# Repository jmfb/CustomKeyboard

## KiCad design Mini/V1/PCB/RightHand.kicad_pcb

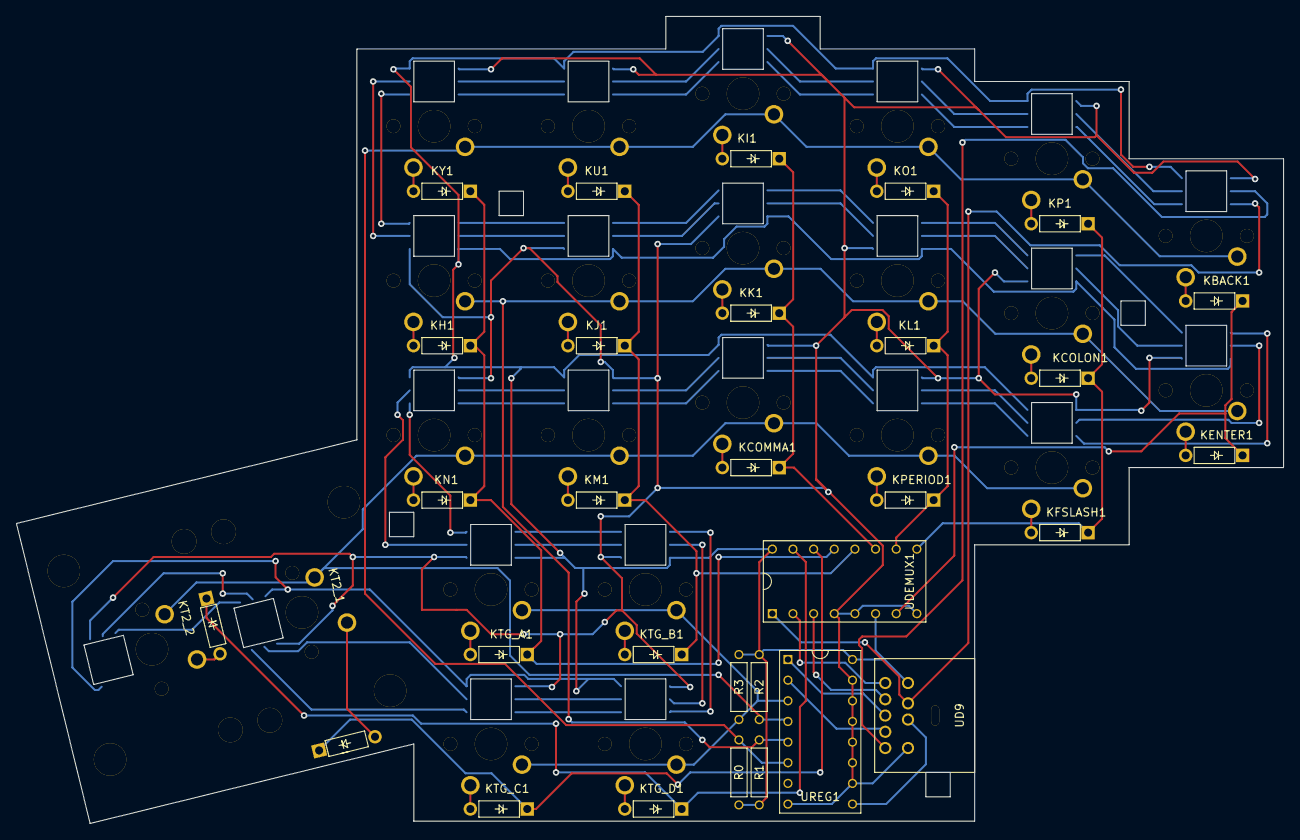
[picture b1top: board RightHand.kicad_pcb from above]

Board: 2 copper layers, 155.9 x 99.3 mm, 30 parts (0 on the bottom side), 88 nets.

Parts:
KBACK1: KeyLedDiode; KeyLedDiodeR2L
KCOLON1: KeyLedDiode; KeyLedDiodeL2R
KCOMMA1: KeyLedDiode; KeyLedDiodeR2L
KENTER1: KeyLedDiode; KeyLedDiodeL2R
KFSLASH1: KeyLedDiode; KeyLedDiodeR2L
KH1: KeyLedDiode; KeyLedDiodeL2R
KI1: KeyLedDiode; KeyLedDiodeR2L
KJ1: KeyLedDiode; KeyLedDiodeL2R
KK1: KeyLedDiode; KeyLedDiodeL2R
KL1: KeyLedDiode; KeyLedDiodeL2R
KM1: KeyLedDiode; KeyLedDiodeR2L
KN1: KeyLedDiode; KeyLedDiodeR2L
KO1: KeyLedDiode; KeyLedDiodeR2L
KP1: KeyLedDiode; KeyLedDiodeR2L
KPERIOD1: KeyLedDiode; KeyLedDiodeR2L
KT2_1: KeyLedDiode; Key2LedDiodeL2R
KT2_2: KeyLedDiode; Key2LedDiodeR2L
KTG_A1: KeyLedDiode; KeyLedDiodeL2R
KTG_B1: KeyLedDiode; KeyLedDiodeL2R
KTG_C1: KeyLedDiode; KeyLedDiodeR2L
KTG_D1: KeyLedDiode; KeyLedDiodeR2L
KU1: KeyLedDiode; KeyLedDiodeR2L
KY1: KeyLedDiode; KeyLedDiodeR2L
R0, R1, R2, R3: R; PullupResistor
UD9: MiniDINN9; MiniDin9
UDEMUX1: Demultiplexer; DualInlineMicrochip2x8
UREG1: ParallelLoadShiftRegister; DualInlineMicrochip2x8

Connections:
C0: KBACK1.1, KI1.1, KO1.1, KP1.1, KU1.1, KY1.1, R0.2, UREG1.6
C1: KCOLON1.1, KENTER1.1, KH1.1, KJ1.1, KK1.1, KL1.1, R1.1, UREG1.5
C2: KCOMMA1.1, KFSLASH1.1, KM1.1, KN1.1, KPERIOD1.1, KT2_1.1, KT2_2.1, R2.1, UREG1.4
C3: KTG_A1.1, KTG_B1.1, KTG_C1.1, KTG_D1.1, R3.1, UREG1.3
CLK_C: UD9.8, UREG1.2
CLK_L: KBACK1.9, UD9.9
GND: KBACK1.8, KCOLON1.8, KCOMMA1.8, KENTER1.8, KFSLASH1.8, KH1.8, KI1.8, KJ1.8, KK1.8, KL1.8, KM1.8, KN1.8, KO1.8, KP1.8, KPERIOD1.8, KT2_1.8, KT2_2.8, KTG_A1.8, KTG_B1.8, KTG_C1.8, KTG_D1.8, KU1.8, KY1.8, UD9.6, UDEMUX1.4, UDEMUX1.5, UDEMUX1.8, UREG1.8, UREG1.10, UREG1.11, UREG1.12, UREG1.13, UREG1.14, UREG1.15
unnamed: KBACK1.2, KBACK1.3
unnamed: KBACK1.6, KP1.9
unnamed: KBACK1.7, KP1.10
unnamed: KCOMMA1.2, KCOMMA1.3
unnamed: KCOMMA1.6, KM1.9
unnamed: KCOMMA1.7, KM1.10
unnamed: KCOMMA1.9, KPERIOD1.6
unnamed: KCOMMA1.10, KPERIOD1.7
unnamed: KENTER1.2, KENTER1.3
unnamed: KENTER1.6, KFSLASH1.9
unnamed: KENTER1.7, KFSLASH1.10
unnamed: KCOLON1.6, KENTER1.9
unnamed: KCOLON1.7, KENTER1.10
unnamed: KFSLASH1.2, KFSLASH1.3
unnamed: KFSLASH1.6, KPERIOD1.9
unnamed: KFSLASH1.7, KPERIOD1.10
unnamed: KH1.2, KH1.3
unnamed: KH1.6, KJ1.9
unnamed: KH1.7, KJ1.10
unnamed: KH1.9, KY1.6
unnamed: KH1.10, KY1.7
unnamed: KI1.2, KI1.3
unnamed: KI1.6, KU1.9
unnamed: KI1.7, KU1.10
unnamed: KI1.9, KO1.6
unnamed: KI1.10, KO1.7
unnamed: KJ1.2, KJ1.3
unnamed: KJ1.6, KK1.9
unnamed: KJ1.7, KK1.10
unnamed: KK1.2, KK1.3
unnamed: KK1.6, KL1.9
unnamed: KK1.7, KL1.10
unnamed: KL1.2, KL1.3
unnamed: KCOLON1.9, KL1.6
unnamed: KCOLON1.10, KL1.7
unnamed: KM1.2, KM1.3
unnamed: KM1.6, KN1.9
unnamed: KM1.7, KN1.10
unnamed: KN1.2, KN1.3
unnamed: KN1.6, KTG_A1.9
unnamed: KN1.7, KTG_A1.10
unnamed: KO1.2, KO1.3
unnamed: KO1.9, KP1.6
unnamed: KO1.10, KP1.7
unnamed: KP1.2, KP1.3
unnamed: KPERIOD1.2, KPERIOD1.3
unnamed: KCOLON1.2, KCOLON1.3
unnamed: KT2_1.2, KT2_1.3
unnamed: KT2_1.6, KT2_2.9
unnamed: KT2_1.7, KT2_2.10
unnamed: KT2_1.9, KTG_C1.6
unnamed: KT2_1.10, KTG_C1.7
unnamed: KT2_2.2, KT2_2.3
unnamed: KTG_A1.2, KTG_A1.3
unnamed: KTG_A1.6, KTG_B1.9
unnamed: KTG_A1.7, KTG_B1.10
unnamed: KTG_B1.2, KTG_B1.3
unnamed: KTG_B1.6, KTG_D1.9
unnamed: KTG_B1.7, KTG_D1.10
unnamed: KTG_C1.2, KTG_C1.3
unnamed: KTG_C1.9, KTG_D1.6
unnamed: KTG_C1.10, KTG_D1.7
unnamed: KTG_D1.2, KTG_D1.3
unnamed: KU1.2, KU1.3
unnamed: KU1.6, KY1.9
unnamed: KU1.7, KY1.10
unnamed: KY1.2, KY1.3
R0: KT2_2.4, KTG_D1.4, UDEMUX1.15
R1: KT2_1.4, KTG_C1.4, UDEMUX1.14
R2: KH1.4, KN1.4, KTG_A1.4, KY1.4, UDEMUX1.13
R3: KJ1.4, KM1.4, KTG_B1.4, KU1.4, UDEMUX1.12
R4: KCOMMA1.4, KI1.4, KK1.4, UDEMUX1.11
R5: KL1.4, KO1.4, KPERIOD1.4, UDEMUX1.10
R6: KCOLON1.4, KFSLASH1.4, KP1.4, UDEMUX1.9
R7: KBACK1.4, KENTER1.4, UDEMUX1.7
RX: UD9.2, UREG1.9
S0_DL: KBACK1.10, UD9.1, UDEMUX1.1
S1: UD9.7, UDEMUX1.2
S2: UD9.4, UDEMUX1.3
SH_LD: UD9.5, UREG1.1
VCC: KBACK1.5, KCOLON1.5, KCOMMA1.5, KENTER1.5, KFSLASH1.5, KH1.5, KI1.5, KJ1.5, KK1.5, KL1.5, KM1.5, KN1.5, KO1.5, KP1.5, KPERIOD1.5, KT2_1.5, KT2_2.5, KTG_A1.5, KTG_B1.5, KTG_C1.5, KTG_D1.5, KU1.5, KY1.5, R0.1, R1.2, R2.2, R3.2, UD9.3, UDEMUX1.6, UDEMUX1.16, UREG1.16

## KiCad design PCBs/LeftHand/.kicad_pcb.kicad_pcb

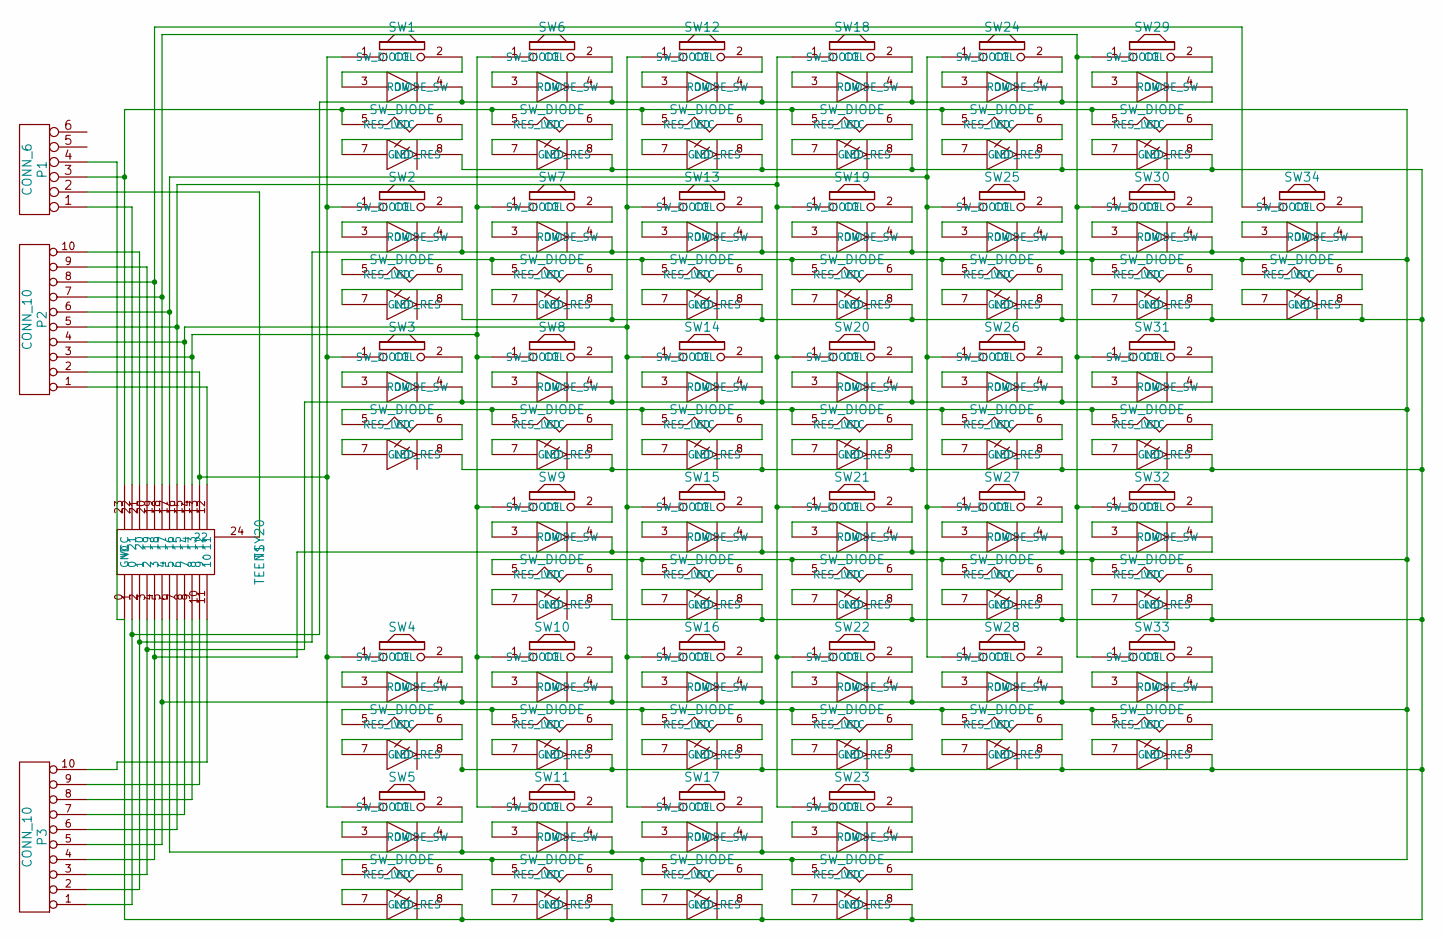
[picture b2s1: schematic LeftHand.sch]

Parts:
P1: CONN_6
P2, P3: CONN_10
SW1, SW2, SW3, SW4, SW5, SW6, SW7, SW8, SW9, SW10, SW11, SW12, SW13, SW14, SW15, SW16, SW17, SW18, SW19, SW20, SW21, SW22, SW23, SW24, SW25, SW26, SW27, SW28, SW29, SW30, SW31, SW32, SW33, SW34: SW_DIODE
T1: TEENSY20

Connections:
unnamed: P3.4, SW9.4 (ROW), SW15.4 (ROW), SW21.4 (ROW), SW27.4 (ROW), SW32.4 (ROW), T1.4 (3)
unnamed: SW5.4 (ROW), SW11.4 (ROW), SW17.4 (ROW), SW23.4 (ROW), T1.6 (5)
unnamed: P3.5, SW4.4 (ROW), SW10.4 (ROW), SW16.4 (ROW), SW22.4 (ROW), SW28.4 (ROW), SW33.4 (ROW), T1.5 (4)
unnamed: P3.3, SW3.4 (ROW), SW8.4 (ROW), SW14.4 (ROW), SW20.4 (ROW), SW26.4 (ROW), SW31.4 (ROW), T1.3 (2)
unnamed: SW11.6 (RES_LED), SW11.7 (LED_RES)
unnamed: SW5.2 (SW_DIODE), SW5.3 (DIODE_SW)
unnamed: SW5.6 (RES_LED), SW5.7 (LED_RES)
unnamed: SW10.2 (SW_DIODE), SW10.3 (DIODE_SW)
unnamed: SW10.6 (RES_LED), SW10.7 (LED_RES)
unnamed: SW11.2 (SW_DIODE), SW11.3 (DIODE_SW)
unnamed: SW16.2 (SW_DIODE), SW16.3 (DIODE_SW)
unnamed: SW16.6 (RES_LED), SW16.7 (LED_RES)
unnamed: SW17.2 (SW_DIODE), SW17.3 (DIODE_SW)
unnamed: SW17.6 (RES_LED), SW17.7 (LED_RES)
unnamed: SW30.6 (RES_LED), SW30.7 (LED_RES)
unnamed: SW31.2 (SW_DIODE), SW31.3 (DIODE_SW)
unnamed: SW31.6 (RES_LED), SW31.7 (LED_RES)
unnamed: SW32.2 (SW_DIODE), SW32.3 (DIODE_SW)
unnamed: SW32.6 (RES_LED), SW32.7 (LED_RES)
unnamed: SW34.2 (SW_DIODE), SW34.3 (DIODE_SW)
unnamed: SW34.6 (RES_LED), SW34.7 (LED_RES)
unnamed: SW4.2 (SW_DIODE), SW4.3 (DIODE_SW)
unnamed: SW4.6 (RES_LED), SW4.7 (LED_RES)
unnamed: SW28.2 (SW_DIODE), SW28.3 (DIODE_SW)
unnamed: SW22.2 (SW_DIODE), SW22.3 (DIODE_SW)
unnamed: SW22.6 (RES_LED), SW22.7 (LED_RES)
unnamed: SW23.2 (SW_DIODE), SW23.3 (DIODE_SW)
unnamed: SW23.6 (RES_LED), SW23.7 (LED_RES)
unnamed: SW28.6 (RES_LED), SW28.7 (LED_RES)
unnamed: SW33.2 (SW_DIODE), SW33.3 (DIODE_SW)
unnamed: SW33.6 (RES_LED), SW33.7 (LED_RES)
unnamed: P2.8, SW34.1 (COL), T1.19 (18)
unnamed: P2.10, T1.21 (20)
unnamed: P2.9, T1.20 (19)
unnamed: P1.1, T1.22 (21)
unnamed: P1.2, T1.24 (22)
unnamed: P3.7, T1.8 (7)
unnamed: P3.6, T1.7 (6)
unnamed: P3.8, T1.9 (8)
unnamed: P3.9, T1.10 (9)
unnamed: P3.10, T1.11 (10)
unnamed: P2.1, T1.12 (11)
unnamed: P3.1, SW1.4 (ROW), SW6.4 (ROW), SW12.4 (ROW), SW18.4 (ROW), SW24.4 (ROW), SW29.4 (ROW), T1.1 (0)
unnamed: P2.7, SW29.1 (COL), SW30.1 (COL), SW31.1 (COL), SW32.1 (COL), SW33.1 (COL), T1.18 (17)
unnamed: P3.2, SW2.4 (ROW), SW7.4 (ROW), SW13.4 (ROW), SW19.4 (ROW), SW25.4 (ROW), SW30.4 (ROW), SW34.4 (ROW), T1.2 (1)
unnamed: P2.6, SW24.1 (COL), SW25.1 (COL), SW26.1 (COL), SW27.1 (COL), SW28.1 (COL), T1.17 (16)
unnamed: P1.3, SW1.5 (VCC), SW2.5 (VCC), SW3.5 (VCC), SW4.5 (VCC), SW5.5 (VCC), SW6.5 (VCC), SW7.5 (VCC), SW8.5 (VCC), SW9.5 (VCC), SW10.5 (VCC), SW11.5 (VCC), SW12.5 (VCC), SW13.5 (VCC), SW14.5 (VCC), SW15.5 (VCC), SW16.5 (VCC), SW17.5 (VCC), SW18.5 (VCC), SW19.5 (VCC), SW20.5 (VCC), SW21.5 (VCC), SW22.5 (VCC), SW23.5 (VCC), SW24.5 (VCC), SW25.5 (VCC), SW26.5 (VCC), SW27.5 (VCC), SW28.5 (VCC), SW29.5 (VCC), SW30.5 (VCC), SW31.5 (VCC), SW32.5 (VCC), SW33.5 (VCC), SW34.5 (VCC), T1.23 (VCC)
unnamed: P2.3, SW6.1 (COL), SW7.1 (COL), SW8.1 (COL), SW9.1 (COL), SW10.1 (COL), SW11.1 (COL), T1.14 (13)
unnamed: P2.2, SW1.1 (COL), SW2.1 (COL), SW3.1 (COL), SW4.1 (COL), SW5.1 (COL), T1.13 (12)
unnamed: P2.5, SW18.1 (COL), SW19.1 (COL), SW20.1 (COL), SW21.1 (COL), SW22.1 (COL), SW23.1 (COL), T1.16 (15)
unnamed: P2.4, SW12.1 (COL), SW13.1 (COL), SW14.1 (COL), SW15.1 (COL), SW16.1 (COL), SW17.1 (COL), T1.15 (14)
unnamed: SW20.2 (SW_DIODE), SW20.3 (DIODE_SW)
unnamed: SW18.6 (RES_LED), SW18.7 (LED_RES)
unnamed: SW19.2 (SW_DIODE), SW19.3 (DIODE_SW)
unnamed: SW19.6 (RES_LED), SW19.7 (LED_RES)
unnamed: SW20.6 (RES_LED), SW20.7 (LED_RES)
unnamed: SW21.2 (SW_DIODE), SW21.3 (DIODE_SW)
unnamed: SW21.6 (RES_LED), SW21.7 (LED_RES)
unnamed: SW15.2 (SW_DIODE), SW15.3 (DIODE_SW)
unnamed: SW15.6 (RES_LED), SW15.7 (LED_RES)
unnamed: SW18.2 (SW_DIODE), SW18.3 (DIODE_SW)
unnamed: SW25.6 (RES_LED), SW25.7 (LED_RES)
unnamed: SW26.2 (SW_DIODE), SW26.3 (DIODE_SW)
unnamed: SW26.6 (RES_LED), SW26.7 (LED_RES)
unnamed: SW27.6 (RES_LED), SW27.7 (LED_RES)
unnamed: SW24.2 (SW_DIODE), SW24.3 (DIODE_SW)
unnamed: SW24.6 (RES_LED), SW24.7 (LED_RES)
unnamed: SW25.2 (SW_DIODE), SW25.3 (DIODE_SW)
unnamed: SW6.2 (SW_DIODE), SW6.3 (DIODE_SW)
unnamed: SW6.6 (RES_LED), SW6.7 (LED_RES)
unnamed: SW7.6 (RES_LED), SW7.7 (LED_RES)
unnamed: SW1.2 (SW_DIODE), SW1.3 (DIODE_SW)
unnamed: SW1.6 (RES_LED), SW1.7 (LED_RES)
unnamed: SW2.2 (SW_DIODE), SW2.3 (DIODE_SW)
unnamed: SW2.6 (RES_LED), SW2.7 (LED_RES)
unnamed: SW3.2 (SW_DIODE), SW3.3 (DIODE_SW)
unnamed: SW3.6 (RES_LED), SW3.7 (LED_RES)
unnamed: SW13.2 (SW_DIODE), SW13.3 (DIODE_SW)
unnamed: SW12.2 (SW_DIODE), SW12.3 (DIODE_SW)
unnamed: SW12.6 (RES_LED), SW12.7 (LED_RES)
unnamed: SW13.6 (RES_LED), SW13.7 (LED_RES)
unnamed: SW14.2 (SW_DIODE), SW14.3 (DIODE_SW)
unnamed: SW14.6 (RES_LED), SW14.7 (LED_RES)
unnamed: SW8.2 (SW_DIODE), SW8.3 (DIODE_SW)
unnamed: SW8.6 (RES_LED), SW8.7 (LED_RES)
unnamed: SW9.2 (SW_DIODE), SW9.3 (DIODE_SW)
unnamed: SW9.6 (RES_LED), SW9.7 (LED_RES)
unnamed: SW7.2 (SW_DIODE), SW7.3 (DIODE_SW)
unnamed: SW27.2 (SW_DIODE), SW27.3 (DIODE_SW)
unnamed: SW29.2 (SW_DIODE), SW29.3 (DIODE_SW)
unnamed: SW29.6 (RES_LED), SW29.7 (LED_RES)
unnamed: SW30.2 (SW_DIODE), SW30.3 (DIODE_SW)

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
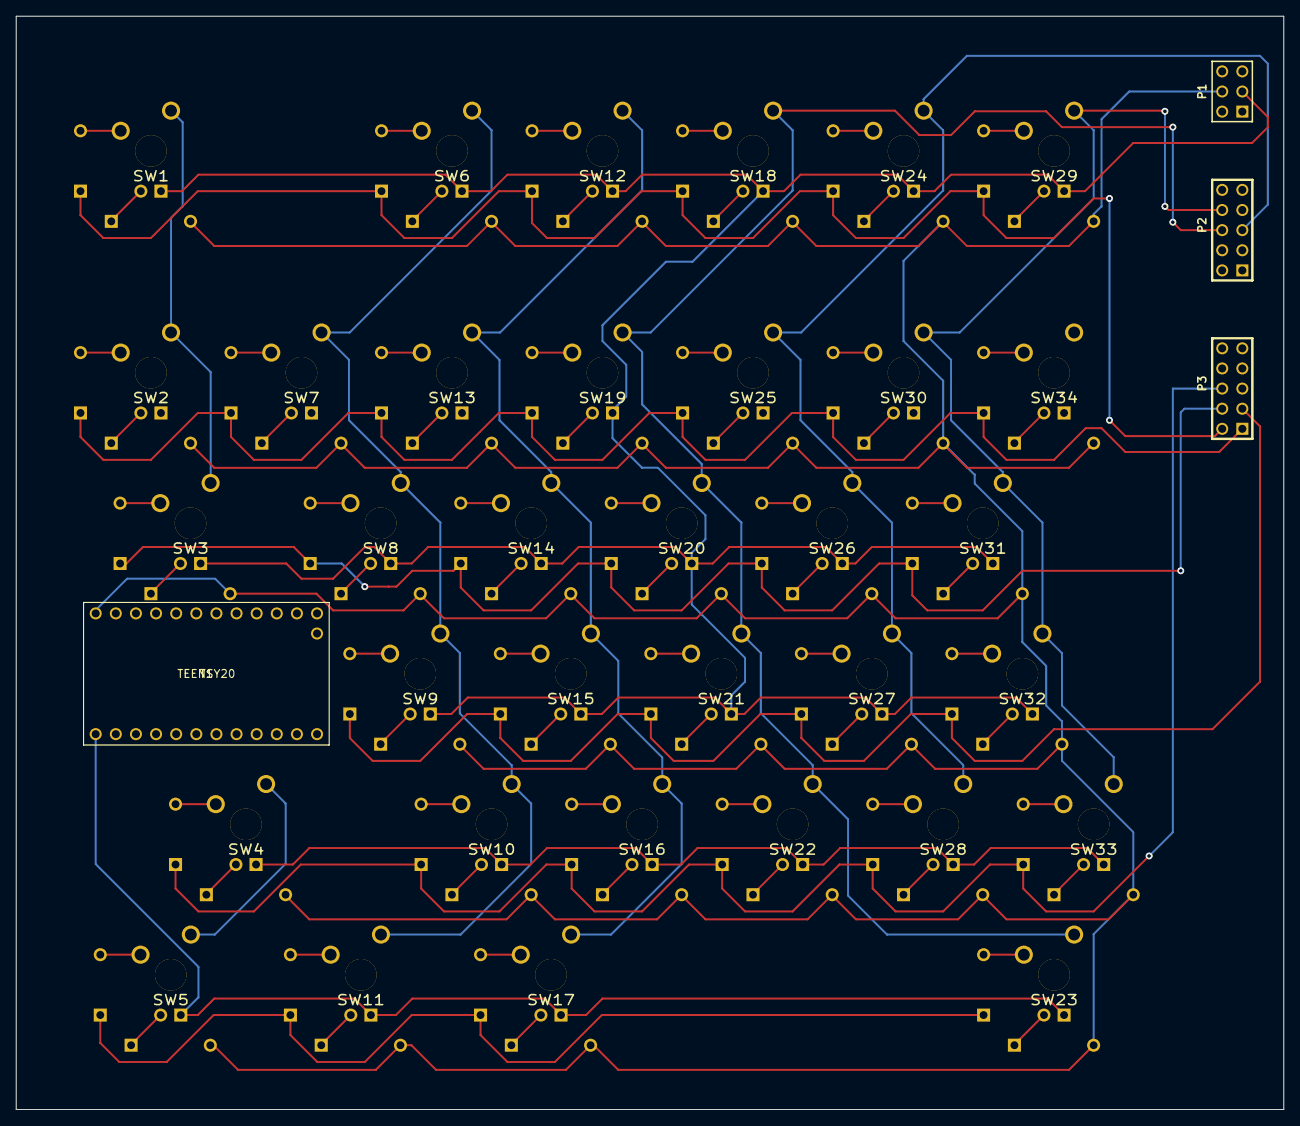
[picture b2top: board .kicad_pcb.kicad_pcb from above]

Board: 2 copper layers, 160.0 x 138.0 mm, 38 parts (0 on the bottom side), 94 nets.

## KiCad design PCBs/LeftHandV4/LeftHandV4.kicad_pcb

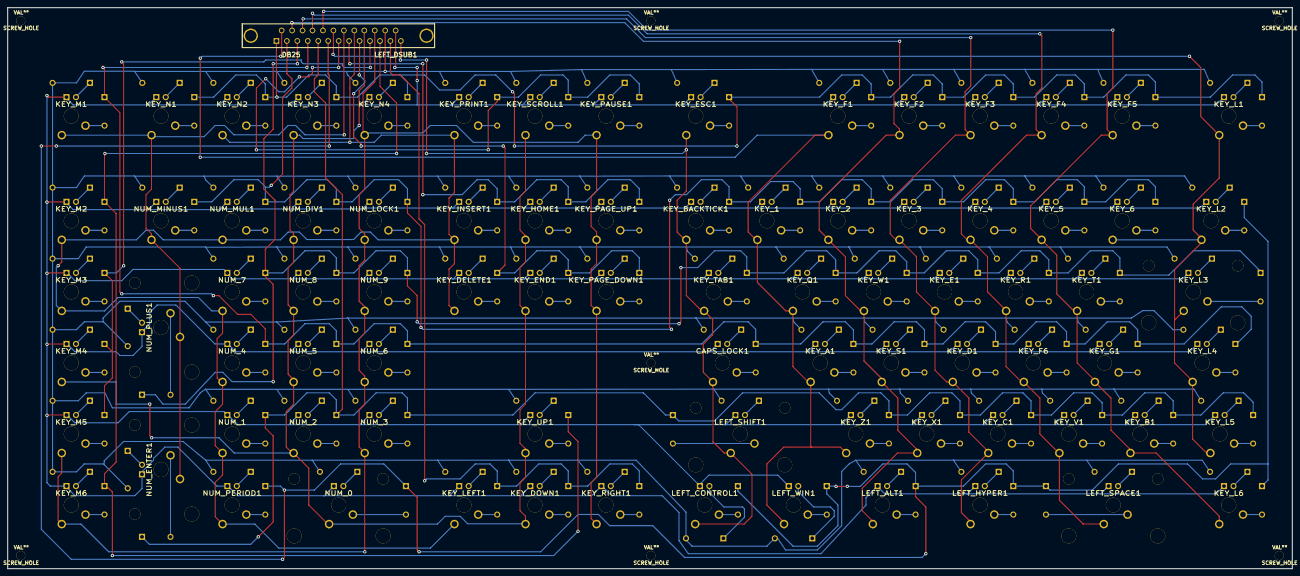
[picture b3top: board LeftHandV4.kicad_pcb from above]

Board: 2 copper layers, 343.5 x 150.0 mm, 90 parts (0 on the bottom side), 189 nets.

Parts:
CAPS_LOCK1: SW_DIODE
KEY_1, KEY_2, KEY_3, KEY_4, KEY_5, KEY_6: SW_DIODE
KEY_A1: SW_DIODE
KEY_B1: SW_DIODE
KEY_BACKTICK1: SW_DIODE
KEY_C1: SW_DIODE
KEY_D1: SW_DIODE
KEY_DELETE1: SW_DIODE
KEY_DOWN1: SW_DIODE
KEY_E1: SW_DIODE
KEY_END1: SW_DIODE
KEY_ESC1: SW_DIODE
KEY_F1, KEY_F2, KEY_F3, KEY_F4, KEY_F5, KEY_F6: SW_DIODE
KEY_G1: SW_DIODE
KEY_HOME1: SW_DIODE
KEY_INSERT1: SW_DIODE
KEY_L1, KEY_L2, KEY_L4, KEY_L5, KEY_L6: SW_DIODE
KEY_L3: SW_DIODE; SW2_DIODE_R
KEY_LEFT1: SW_DIODE
KEY_M1, KEY_M2, KEY_M3, KEY_M4, KEY_M5, KEY_M6: SW_DIODE
KEY_N1, KEY_N2, KEY_N3, KEY_N4: SW_DIODE
KEY_PAGE_DOWN1: SW_DIODE
KEY_PAGE_UP1: SW_DIODE
KEY_PAUSE1: SW_DIODE
KEY_PRINT1: SW_DIODE
KEY_Q1: SW_DIODE
KEY_R1: SW_DIODE
KEY_RIGHT1: SW_DIODE
KEY_S1: SW_DIODE
KEY_SCROLL1: SW_DIODE
KEY_T1: SW_DIODE
KEY_TAB1: SW_DIODE
KEY_UP1: SW_DIODE
KEY_V1: SW_DIODE
KEY_W1: SW_DIODE
KEY_X1: SW_DIODE
KEY_Z1: SW_DIODE
LEFT_ALT1: SW_DIODE
LEFT_CONTROL1: SW_DIODE; SW_DIODE_RTOP
LEFT_DSUB1: DB25; DB25FD
LEFT_HYPER1: SW_DIODE
LEFT_SHIFT1: SW_DIODE; SW2_DIODE_L
LEFT_SPACE1: SW_DIODE; SW2_DIODE_L
LEFT_WIN1: SW_DIODE; SW_DIODE_RTOP
NUM_0: SW_DIODE; SW2_DIODE_R
NUM_1, NUM_2, NUM_3, NUM_4, NUM_5, NUM_6, NUM_7, NUM_8, NUM_9: SW_DIODE
NUM_DIV1: SW_DIODE
NUM_ENTER1: SW_DIODE; SW2_DIODE_L
NUM_LOCK1: SW_DIODE
NUM_MINUS1: SW_DIODE
NUM_MUL1: SW_DIODE
NUM_PERIOD1: SW_DIODE
NUM_PLUS1: SW_DIODE; SW2_DIODE_L
SCREW_HOLE: VAL**; SCREW_HOLE
SCREW_HOLE#2, SCREW_HOLE#3, SCREW_HOLE#4, SCREW_HOLE#5, SCREW_HOLE#6, SCREW_HOLE#7: VAL**; SCREW_HOLE

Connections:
unnamed: LEFT_SPACE1.6, LEFT_SPACE1.7
unnamed: KEY_L6.2, KEY_L6.3
unnamed: KEY_L6.6, KEY_L6.7
unnamed: CAPS_LOCK1.8, KEY_1.8, KEY_2.8, KEY_3.8, KEY_4.8, KEY_5.8, KEY_6.8, KEY_A1.8, KEY_B1.8, KEY_BACKTICK1.8, KEY_C1.8, KEY_D1.8, KEY_DELETE1.8, KEY_DOWN1.8, KEY_E1.8, KEY_END1.8, KEY_ESC1.8, KEY_F1.8, KEY_F2.8, KEY_F3.8, KEY_F4.8, KEY_F5.8, KEY_F6.8, KEY_G1.8, KEY_HOME1.8, KEY_INSERT1.8, KEY_L1.8, KEY_L2.8, KEY_L3.8, KEY_L4.8, KEY_L5.8, KEY_L6.8, KEY_LEFT1.8, KEY_M1.8, KEY_M2.8, KEY_M3.8, KEY_M4.8, KEY_M5.8, KEY_M6.8, KEY_N1.8, KEY_N2.8, KEY_N3.8, KEY_N4.8, KEY_PAGE_DOWN1.8, KEY_PAGE_UP1.8, KEY_PAUSE1.8, KEY_PRINT1.8, KEY_Q1.8, KEY_R1.8, KEY_RIGHT1.8, KEY_S1.8, KEY_SCROLL1.8, KEY_T1.8, KEY_TAB1.8, KEY_UP1.8, KEY_V1.8, KEY_W1.8, KEY_X1.8, KEY_Z1.8, LEFT_ALT1.8, LEFT_CONTROL1.8, LEFT_DSUB1.25, LEFT_HYPER1.8, LEFT_SHIFT1.8, LEFT_SPACE1.8, LEFT_WIN1.8, NUM_0.8, NUM_1.8, NUM_2.8, NUM_3.8, NUM_4.8, NUM_5.8, NUM_6.8, NUM_7.8, NUM_8.8, NUM_9.8, NUM_DIV1.8, NUM_ENTER1.8, NUM_LOCK1.8, NUM_MINUS1.8, NUM_MUL1.8, NUM_PERIOD1.8, NUM_PLUS1.8
unnamed: KEY_ESC1.4, KEY_F1.4, KEY_F2.4, KEY_F3.4, KEY_F4.4, KEY_F5.4, KEY_L1.4, KEY_N1.4, KEY_N2.4, KEY_N3.4, KEY_N4.4, LEFT_DSUB1.1
unnamed: KEY_1.4, KEY_2.4, KEY_3.4, KEY_4.4, KEY_5.4, KEY_6.4, KEY_BACKTICK1.4, LEFT_DSUB1.2, NUM_DIV1.4, NUM_LOCK1.4, NUM_MINUS1.4, NUM_MUL1.4
unnamed: KEY_E1.4, KEY_L3.4, KEY_Q1.4, KEY_R1.4, KEY_T1.4, KEY_TAB1.4, KEY_W1.4, LEFT_DSUB1.3, NUM_7.4, NUM_8.4, NUM_9.4, NUM_PLUS1.4
unnamed: CAPS_LOCK1.4, KEY_A1.4, KEY_D1.4, KEY_F6.4, KEY_G1.4, KEY_L4.4, KEY_M1.4, KEY_S1.4, LEFT_DSUB1.4, NUM_4.4, NUM_5.4, NUM_6.4
unnamed: NUM_ENTER1.6, NUM_ENTER1.7
unnamed: KEY_M5.2, KEY_M5.3
unnamed: KEY_M5.6, KEY_M5.7
unnamed: KEY_M6.2, KEY_M6.3
unnamed: KEY_M6.6, KEY_M6.7
unnamed: NUM_ENTER1.2, NUM_ENTER1.3
unnamed: NUM_4.2, NUM_4.3
unnamed: NUM_4.6, NUM_4.7
unnamed: NUM_1.2, NUM_1.3
unnamed: NUM_1.6, NUM_1.7
unnamed: NUM_9.2, NUM_9.3
unnamed: NUM_9.6, NUM_9.7
unnamed: KEY_DELETE1.2, KEY_DELETE1.3
unnamed: KEY_DELETE1.6, KEY_DELETE1.7
unnamed: KEY_END1.2, KEY_END1.3
unnamed: NUM_PERIOD1.2, NUM_PERIOD1.3
unnamed: KEY_END1.6, KEY_END1.7
unnamed: KEY_PAGE_DOWN1.2, KEY_PAGE_DOWN1.3
unnamed: KEY_PAGE_DOWN1.6, KEY_PAGE_DOWN1.7
unnamed: KEY_M4.2, KEY_M4.3
unnamed: KEY_M4.6, KEY_M4.7
unnamed: KEY_UP1.6, KEY_UP1.7
unnamed: NUM_0.2, NUM_0.3
unnamed: NUM_0.6, NUM_0.7
unnamed: KEY_LEFT1.2, KEY_LEFT1.3
unnamed: KEY_LEFT1.6, KEY_LEFT1.7
unnamed: KEY_UP1.2, KEY_UP1.3
unnamed: KEY_DOWN1.2, KEY_DOWN1.3
unnamed: KEY_DOWN1.6, KEY_DOWN1.7
unnamed: KEY_RIGHT1.2, KEY_RIGHT1.3
unnamed: KEY_RIGHT1.6, KEY_RIGHT1.7
unnamed: KEY_ESC1.2, KEY_ESC1.3
unnamed: NUM_2.6, NUM_2.7
unnamed: NUM_PERIOD1.6, NUM_PERIOD1.7
unnamed: NUM_5.2, NUM_5.3
unnamed: NUM_5.6, NUM_5.7
unnamed: NUM_2.2, NUM_2.3
unnamed: NUM_6.2, NUM_6.3
unnamed: NUM_6.6, NUM_6.7
unnamed: NUM_3.2, NUM_3.3
unnamed: NUM_3.6, NUM_3.7
unnamed: KEY_SCROLL1.6, KEY_SCROLL1.7
unnamed: KEY_N1.6, KEY_N1.7
unnamed: KEY_N2.6, KEY_N2.7
unnamed: KEY_N3.6, KEY_N3.7
unnamed: KEY_N4.6, KEY_N4.7
unnamed: KEY_PRINT1.6, KEY_PRINT1.7
unnamed: KEY_PAUSE1.6, KEY_PAUSE1.7
unnamed: KEY_M2.2, KEY_M2.3
unnamed: KEY_M2.6, KEY_M2.7
unnamed: NUM_MINUS1.2, NUM_MINUS1.3
unnamed: NUM_MINUS1.6, NUM_MINUS1.7
unnamed: KEY_N4.2, KEY_N4.3
unnamed: CAPS_LOCK1.5, KEY_1.5, KEY_2.5, KEY_3.5, KEY_4.5, KEY_5.5, KEY_6.5, KEY_A1.5, KEY_B1.5, KEY_BACKTICK1.5, KEY_C1.5, KEY_D1.5, KEY_DELETE1.5, KEY_DOWN1.5, KEY_E1.5, KEY_END1.5, KEY_ESC1.5, KEY_F1.5, KEY_F2.5, KEY_F3.5, KEY_F4.5, KEY_F5.5, KEY_F6.5, KEY_G1.5, KEY_HOME1.5, KEY_INSERT1.5, KEY_L1.5, KEY_L2.5, KEY_L3.5, KEY_L4.5, KEY_L5.5, KEY_L6.5, KEY_LEFT1.5, KEY_M1.5, KEY_M2.5, KEY_M3.5, KEY_M4.5, KEY_M5.5, KEY_M6.5, KEY_N1.5, KEY_N2.5, KEY_N3.5, KEY_N4.5, KEY_PAGE_DOWN1.5, KEY_PAGE_UP1.5, KEY_PAUSE1.5, KEY_PRINT1.5, KEY_Q1.5, KEY_R1.5, KEY_RIGHT1.5, KEY_S1.5, KEY_SCROLL1.5, KEY_T1.5, KEY_TAB1.5, KEY_UP1.5, KEY_V1.5, KEY_W1.5, KEY_X1.5, KEY_Z1.5, LEFT_ALT1.5, LEFT_CONTROL1.5, LEFT_DSUB1.24, LEFT_HYPER1.5, LEFT_SHIFT1.5, LEFT_SPACE1.5, LEFT_WIN1.5, NUM_0.5, NUM_1.5, NUM_2.5, NUM_3.5, NUM_4.5, NUM_5.5, NUM_6.5, NUM_7.5, NUM_8.5, NUM_9.5, NUM_DIV1.5, NUM_ENTER1.5, NUM_LOCK1.5, NUM_MINUS1.5, NUM_MUL1.5, NUM_PERIOD1.5, NUM_PLUS1.5
unnamed: KEY_M1.2, KEY_M1.3
unnamed: KEY_N1.2, KEY_N1.3
unnamed: KEY_N2.2, KEY_N2.3
unnamed: KEY_N3.2, KEY_N3.3
unnamed: KEY_PRINT1.2, KEY_PRINT1.3
unnamed: KEY_SCROLL1.2, KEY_SCROLL1.3
unnamed: KEY_PAUSE1.2, KEY_PAUSE1.3
unnamed: KEY_M1.6, KEY_M1.7
unnamed: KEY_HOME1.6, KEY_HOME1.7
unnamed: KEY_PAGE_UP1.2, KEY_PAGE_UP1.3
unnamed: KEY_PAGE_UP1.6, KEY_PAGE_UP1.7
unnamed: KEY_M3.2, KEY_M3.3
unnamed: KEY_M3.6, KEY_M3.7
unnamed: NUM_PLUS1.2, NUM_PLUS1.3
unnamed: NUM_7.2, NUM_7.3
unnamed: NUM_7.6, NUM_7.7
unnamed: NUM_PLUS1.6, NUM_PLUS1.7
unnamed: NUM_8.2, NUM_8.3
unnamed: NUM_8.6, NUM_8.7
unnamed: NUM_LOCK1.2, NUM_LOCK1.3
unnamed: NUM_MUL1.2, NUM_MUL1.3
unnamed: NUM_MUL1.6, NUM_MUL1.7
unnamed: NUM_DIV1.2, NUM_DIV1.3
unnamed: NUM_DIV1.6, NUM_DIV1.7
unnamed: NUM_LOCK1.6, NUM_LOCK1.7
unnamed: KEY_INSERT1.2, KEY_INSERT1.3
unnamed: KEY_INSERT1.6, KEY_INSERT1.7
unnamed: KEY_HOME1.2, KEY_HOME1.3
unnamed: KEY_L4.2, KEY_L4.3
unnamed: KEY_D1.6, KEY_D1.7
unnamed: KEY_F6.2, KEY_F6.3
unnamed: KEY_F6.6, KEY_F6.7
unnamed: KEY_G1.2, KEY_G1.3
unnamed: KEY_G1.6, KEY_G1.7
unnamed: KEY_L4.6, KEY_L4.7
unnamed: LEFT_SHIFT1.2, LEFT_SHIFT1.3
unnamed: LEFT_SHIFT1.6, LEFT_SHIFT1.7
unnamed: KEY_Z1.2, KEY_Z1.3
unnamed: KEY_T1.6, KEY_T1.7
unnamed: KEY_L3.2, KEY_L3.3
unnamed: KEY_L3.6, KEY_L3.7
unnamed: CAPS_LOCK1.2, CAPS_LOCK1.3
unnamed: CAPS_LOCK1.6, CAPS_LOCK1.7
unnamed: KEY_Z1.6, KEY_Z1.7
unnamed: KEY_A1.2, KEY_A1.3
unnamed: KEY_A1.6, KEY_A1.7
unnamed: KEY_S1.2, KEY_S1.3
unnamed: KEY_S1.6, KEY_S1.7
unnamed: KEY_D1.2, KEY_D1.3
unnamed: LEFT_ALT1.2, LEFT_ALT1.3
unnamed: KEY_L5.6, KEY_L5.7
unnamed: LEFT_CONTROL1.2, LEFT_CONTROL1.3
unnamed: LEFT_CONTROL1.6, LEFT_CONTROL1.7
unnamed: LEFT_WIN1.2, LEFT_WIN1.3
unnamed: LEFT_WIN1.6, LEFT_WIN1.7
unnamed: LEFT_ALT1.6, LEFT_ALT1.7
unnamed: LEFT_HYPER1.2, LEFT_HYPER1.3
unnamed: LEFT_HYPER1.6, LEFT_HYPER1.7
unnamed: LEFT_SPACE1.2, LEFT_SPACE1.3
unnamed: KEY_V1.2, KEY_V1.3
unnamed: KEY_X1.2, KEY_X1.3
unnamed: KEY_X1.6, KEY_X1.7
unnamed: KEY_C1.2, KEY_C1.3
unnamed: KEY_C1.6, KEY_C1.7
unnamed: KEY_V1.6, KEY_V1.7
unnamed: KEY_B1.2, KEY_B1.3
unnamed: KEY_B1.6, KEY_B1.7
unnamed: KEY_L5.2, KEY_L5.3
unnamed: KEY_F5.2, KEY_F5.3
unnamed: KEY_F5.6, KEY_F5.7
unnamed: KEY_L1.2, KEY_L1.3
unnamed: KEY_L1.6, KEY_L1.7
unnamed: KEY_L2.2, KEY_L2.3
unnamed: KEY_L2.6, KEY_L2.7
unnamed: KEY_BACKTICK1.2, KEY_BACKTICK1.3
unnamed: KEY_BACKTICK1.6, KEY_BACKTICK1.7
unnamed: KEY_1.2, KEY_1.3
unnamed: KEY_1.6, KEY_1.7
unnamed: KEY_2.2, KEY_2.3
unnamed: KEY_F2.6, KEY_F2.7
unnamed: KEY_ESC1.6, KEY_ESC1.7
unnamed: KEY_F1.2, KEY_F1.3
unnamed: KEY_F1.6, KEY_F1.7
unnamed: KEY_F2.2, KEY_F2.3
unnamed: KEY_F3.2, KEY_F3.3
unnamed: KEY_F3.6, KEY_F3.7
unnamed: KEY_F4.2, KEY_F4.3
unnamed: KEY_F4.6, KEY_F4.7
unnamed: KEY_TAB1.6, KEY_TAB1.7
unnamed: KEY_Q1.2, KEY_Q1.3
unnamed: KEY_Q1.6, KEY_Q1.7
unnamed: KEY_W1.2, KEY_W1.3
unnamed: KEY_W1.6, KEY_W1.7
unnamed: KEY_E1.2, KEY_E1.3
unnamed: KEY_E1.6, KEY_E1.7
unnamed: KEY_R1.2, KEY_R1.3
unnamed: KEY_R1.6, KEY_R1.7
unnamed: KEY_T1.2, KEY_T1.3
unnamed: KEY_2.6, KEY_2.7
unnamed: KEY_3.2, KEY_3.3
unnamed: KEY_3.6, KEY_3.7
unnamed: KEY_4.2, KEY_4.3
unnamed: KEY_4.6, KEY_4.7
unnamed: KEY_5.2, KEY_5.3
unnamed: KEY_5.6, KEY_5.7
unnamed: KEY_6.2, KEY_6.3
unnamed: KEY_6.6, KEY_6.7
unnamed: KEY_TAB1.2, KEY_TAB1.3
unnamed: CAPS_LOCK1.1, KEY_BACKTICK1.1, KEY_ESC1.1, KEY_TAB1.1, LEFT_CONTROL1.1, LEFT_DSUB1.13, LEFT_SHIFT1.1
unnamed: KEY_1.1, KEY_A1.1, KEY_F1.1, KEY_Q1.1, KEY_Z1.1, LEFT_DSUB1.14, LEFT_WIN1.1
unnamed: KEY_DOWN1.4, KEY_LEFT1.4, KEY_RIGHT1.4, LEFT_DSUB1.12
unnamed: KEY_5.1, KEY_B1.1, KEY_F5.1, KEY_G1.1, KEY_L6.1, KEY_T1.1, LEFT_DSUB1.18
unnamed: KEY_3.1, KEY_C1.1, KEY_D1.1, KEY_E1.1, KEY_F3.1, LEFT_DSUB1.16, LEFT_HYPER1.1
unnamed: KEY_DOWN1.1, KEY_END1.1, KEY_HOME1.1, KEY_M4.1, KEY_N3.1, KEY_SCROLL1.1, KEY_UP1.1, LEFT_DSUB1.22, NUM_0.1, NUM_2.1, NUM_5.1, NUM_8.1, NUM_DIV1.1
unnamed: KEY_6.1, KEY_L1.1, KEY_L2.1, KEY_L3.1, KEY_L4.1, KEY_L5.1, LEFT_DSUB1.19
unnamed: KEY_DELETE1.1, KEY_INSERT1.1, KEY_LEFT1.1, KEY_M2.1, KEY_M3.1, KEY_N2.1, KEY_PRINT1.1, LEFT_DSUB1.21, NUM_1.1, NUM_4.1, NUM_7.1, NUM_MUL1.1, NUM_PERIOD1.1
unnamed: KEY_M5.1, KEY_M6.1, KEY_N4.1, KEY_PAGE_DOWN1.1, KEY_PAGE_UP1.1, KEY_PAUSE1.1, KEY_RIGHT1.1, LEFT_DSUB1.23, NUM_3.1, NUM_6.1, NUM_9.1, NUM_LOCK1.1
unnamed: KEY_4.1, KEY_F4.1, KEY_F6.1, KEY_R1.1, KEY_V1.1, LEFT_DSUB1.17, LEFT_SPACE1.1
unnamed: KEY_2.1, KEY_F2.1, KEY_S1.1, KEY_W1.1, KEY_X1.1, LEFT_ALT1.1, LEFT_DSUB1.15
unnamed: KEY_M1.1, KEY_N1.1, LEFT_DSUB1.20, NUM_ENTER1.1, NUM_MINUS1.1, NUM_PLUS1.1
unnamed: KEY_PAUSE1.4, KEY_PRINT1.4, KEY_SCROLL1.4, LEFT_DSUB1.7
unnamed: KEY_HOME1.4, KEY_INSERT1.4, KEY_PAGE_UP1.4, LEFT_DSUB1.8
unnamed: KEY_DELETE1.4, KEY_END1.4, KEY_PAGE_DOWN1.4, LEFT_DSUB1.9
unnamed: KEY_B1.4, KEY_C1.4, KEY_L5.4, KEY_V1.4, KEY_X1.4, KEY_Z1.4, LEFT_DSUB1.5, LEFT_SHIFT1.4, NUM_1.4, NUM_2.4, NUM_3.4, NUM_ENTER1.4
unnamed: KEY_L2.4, KEY_L6.4, LEFT_ALT1.4, LEFT_CONTROL1.4, LEFT_DSUB1.6, LEFT_HYPER1.4, LEFT_SPACE1.4, LEFT_WIN1.4, NUM_0.4, NUM_PERIOD1.4
unnamed: KEY_M3.4, KEY_M4.4, KEY_M5.4, LEFT_DSUB1.10
unnamed: KEY_M2.4, KEY_M6.4, KEY_UP1.4, LEFT_DSUB1.11
